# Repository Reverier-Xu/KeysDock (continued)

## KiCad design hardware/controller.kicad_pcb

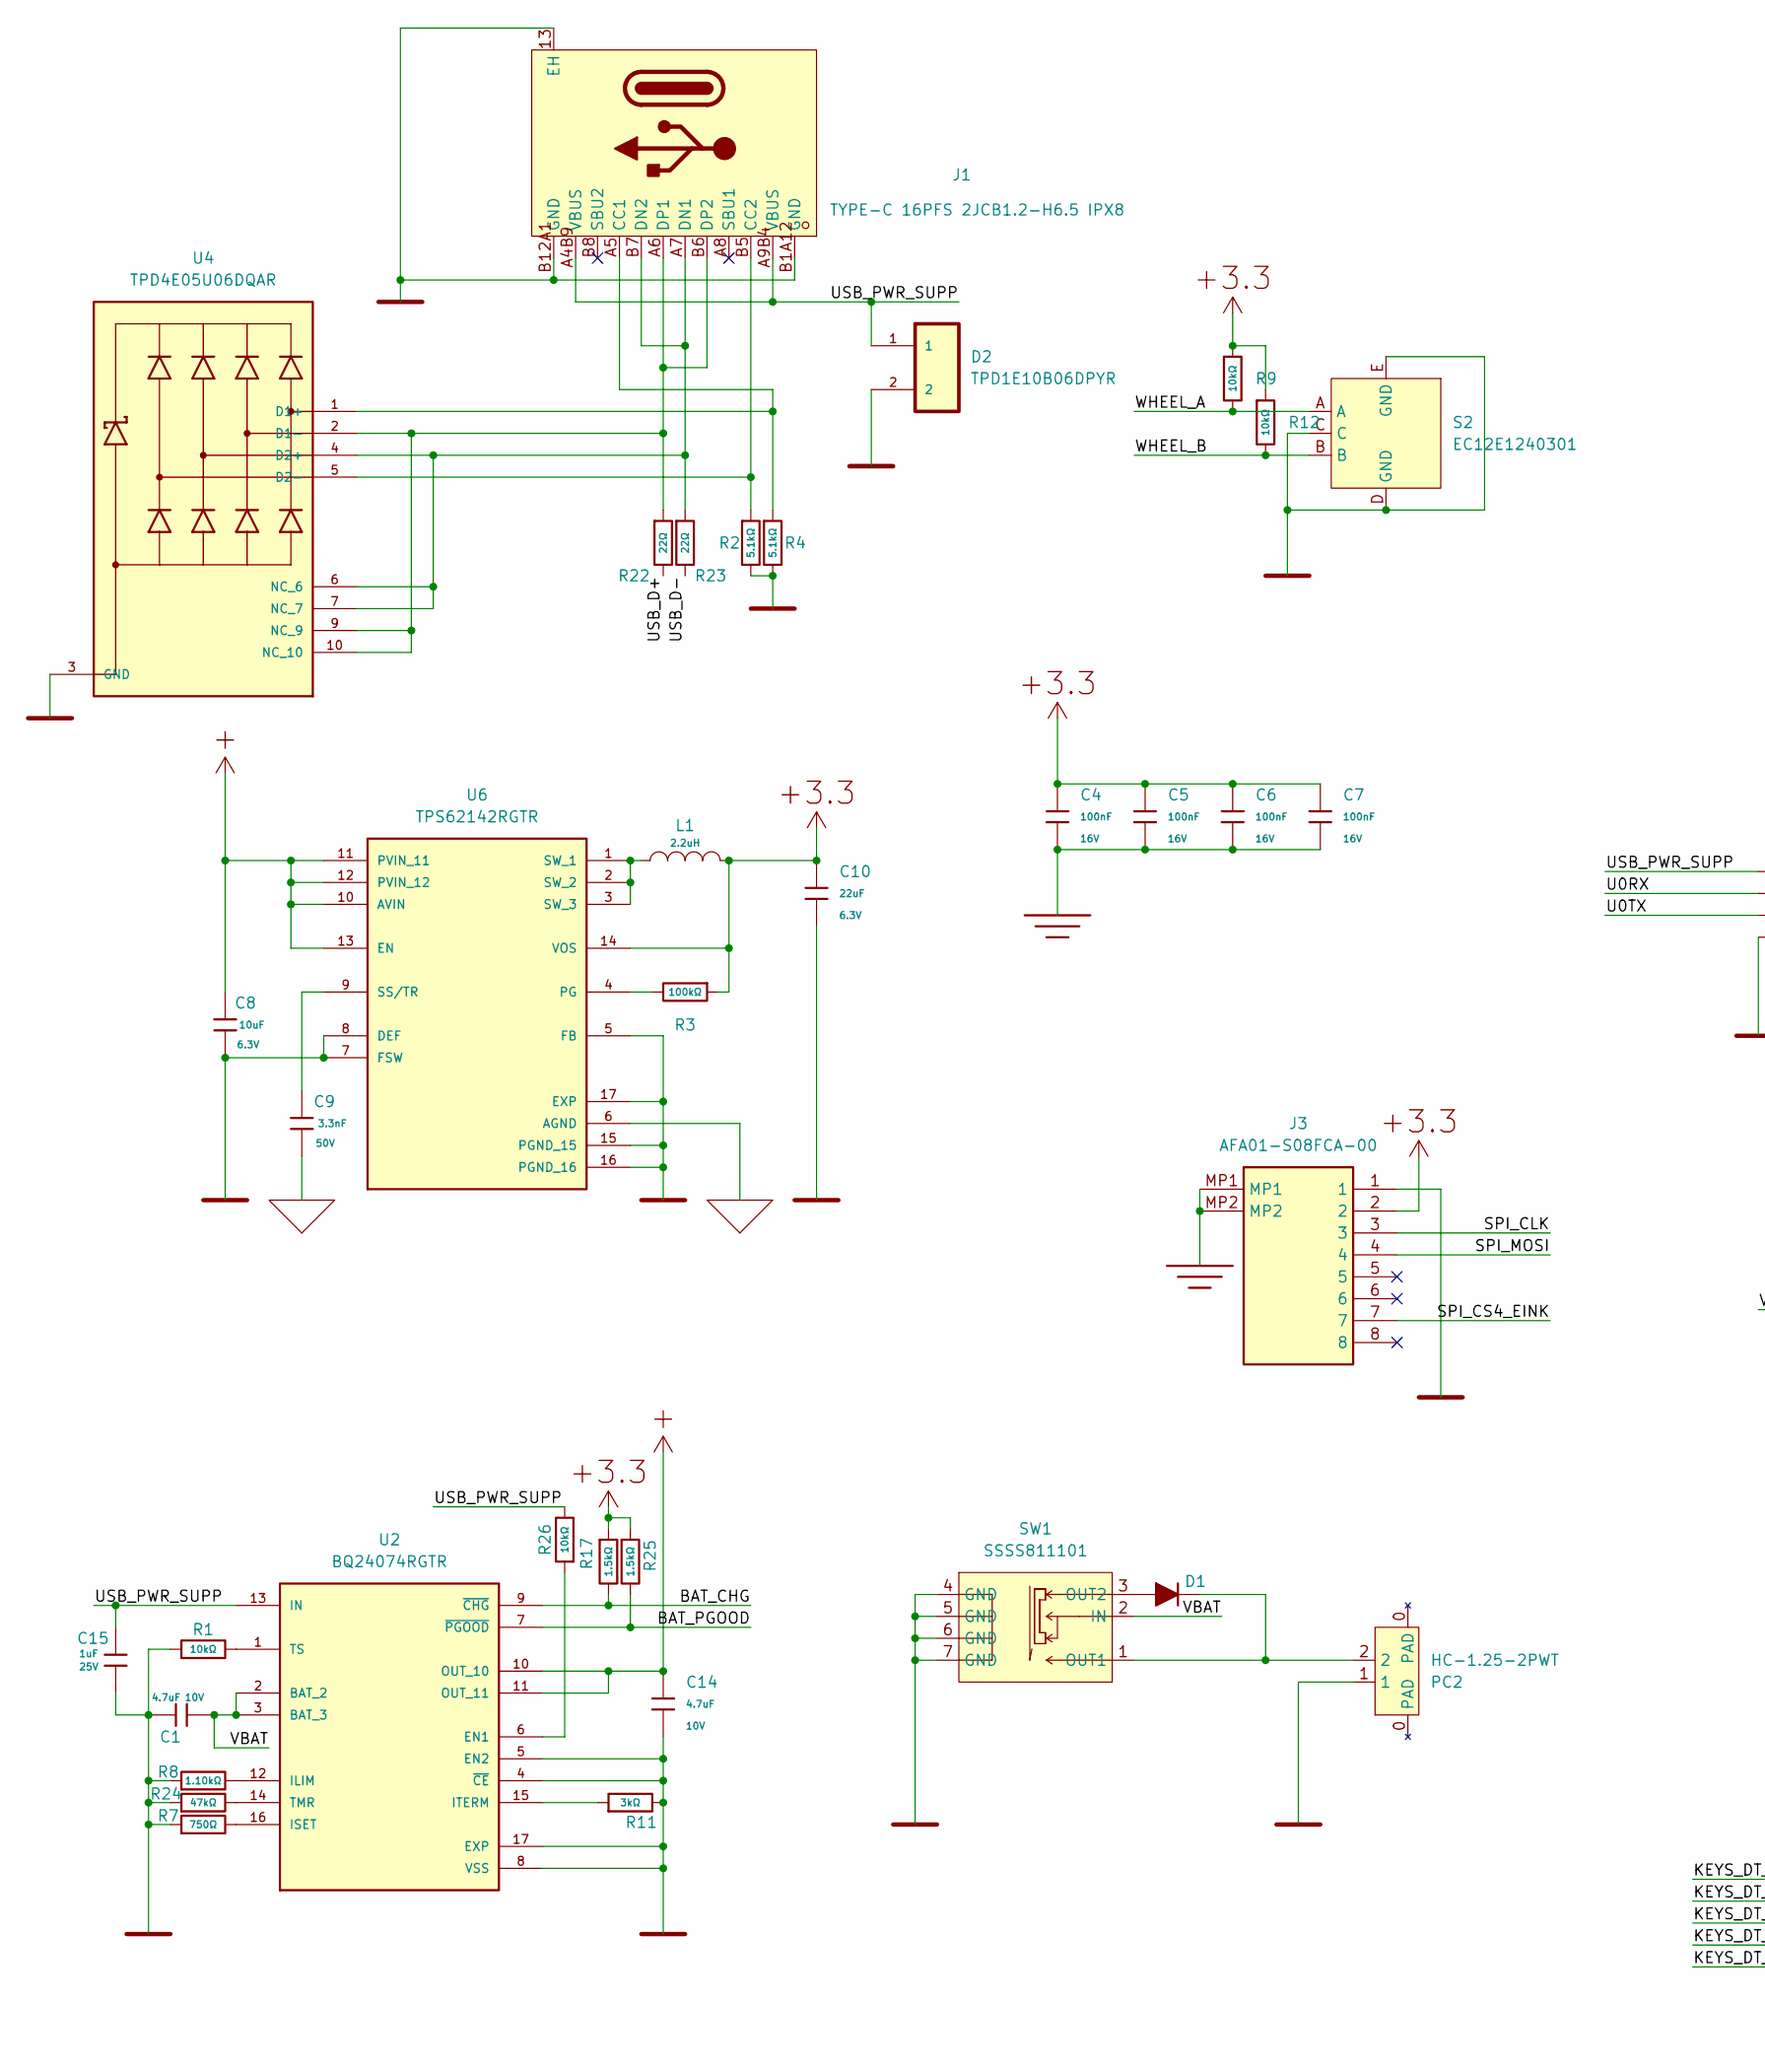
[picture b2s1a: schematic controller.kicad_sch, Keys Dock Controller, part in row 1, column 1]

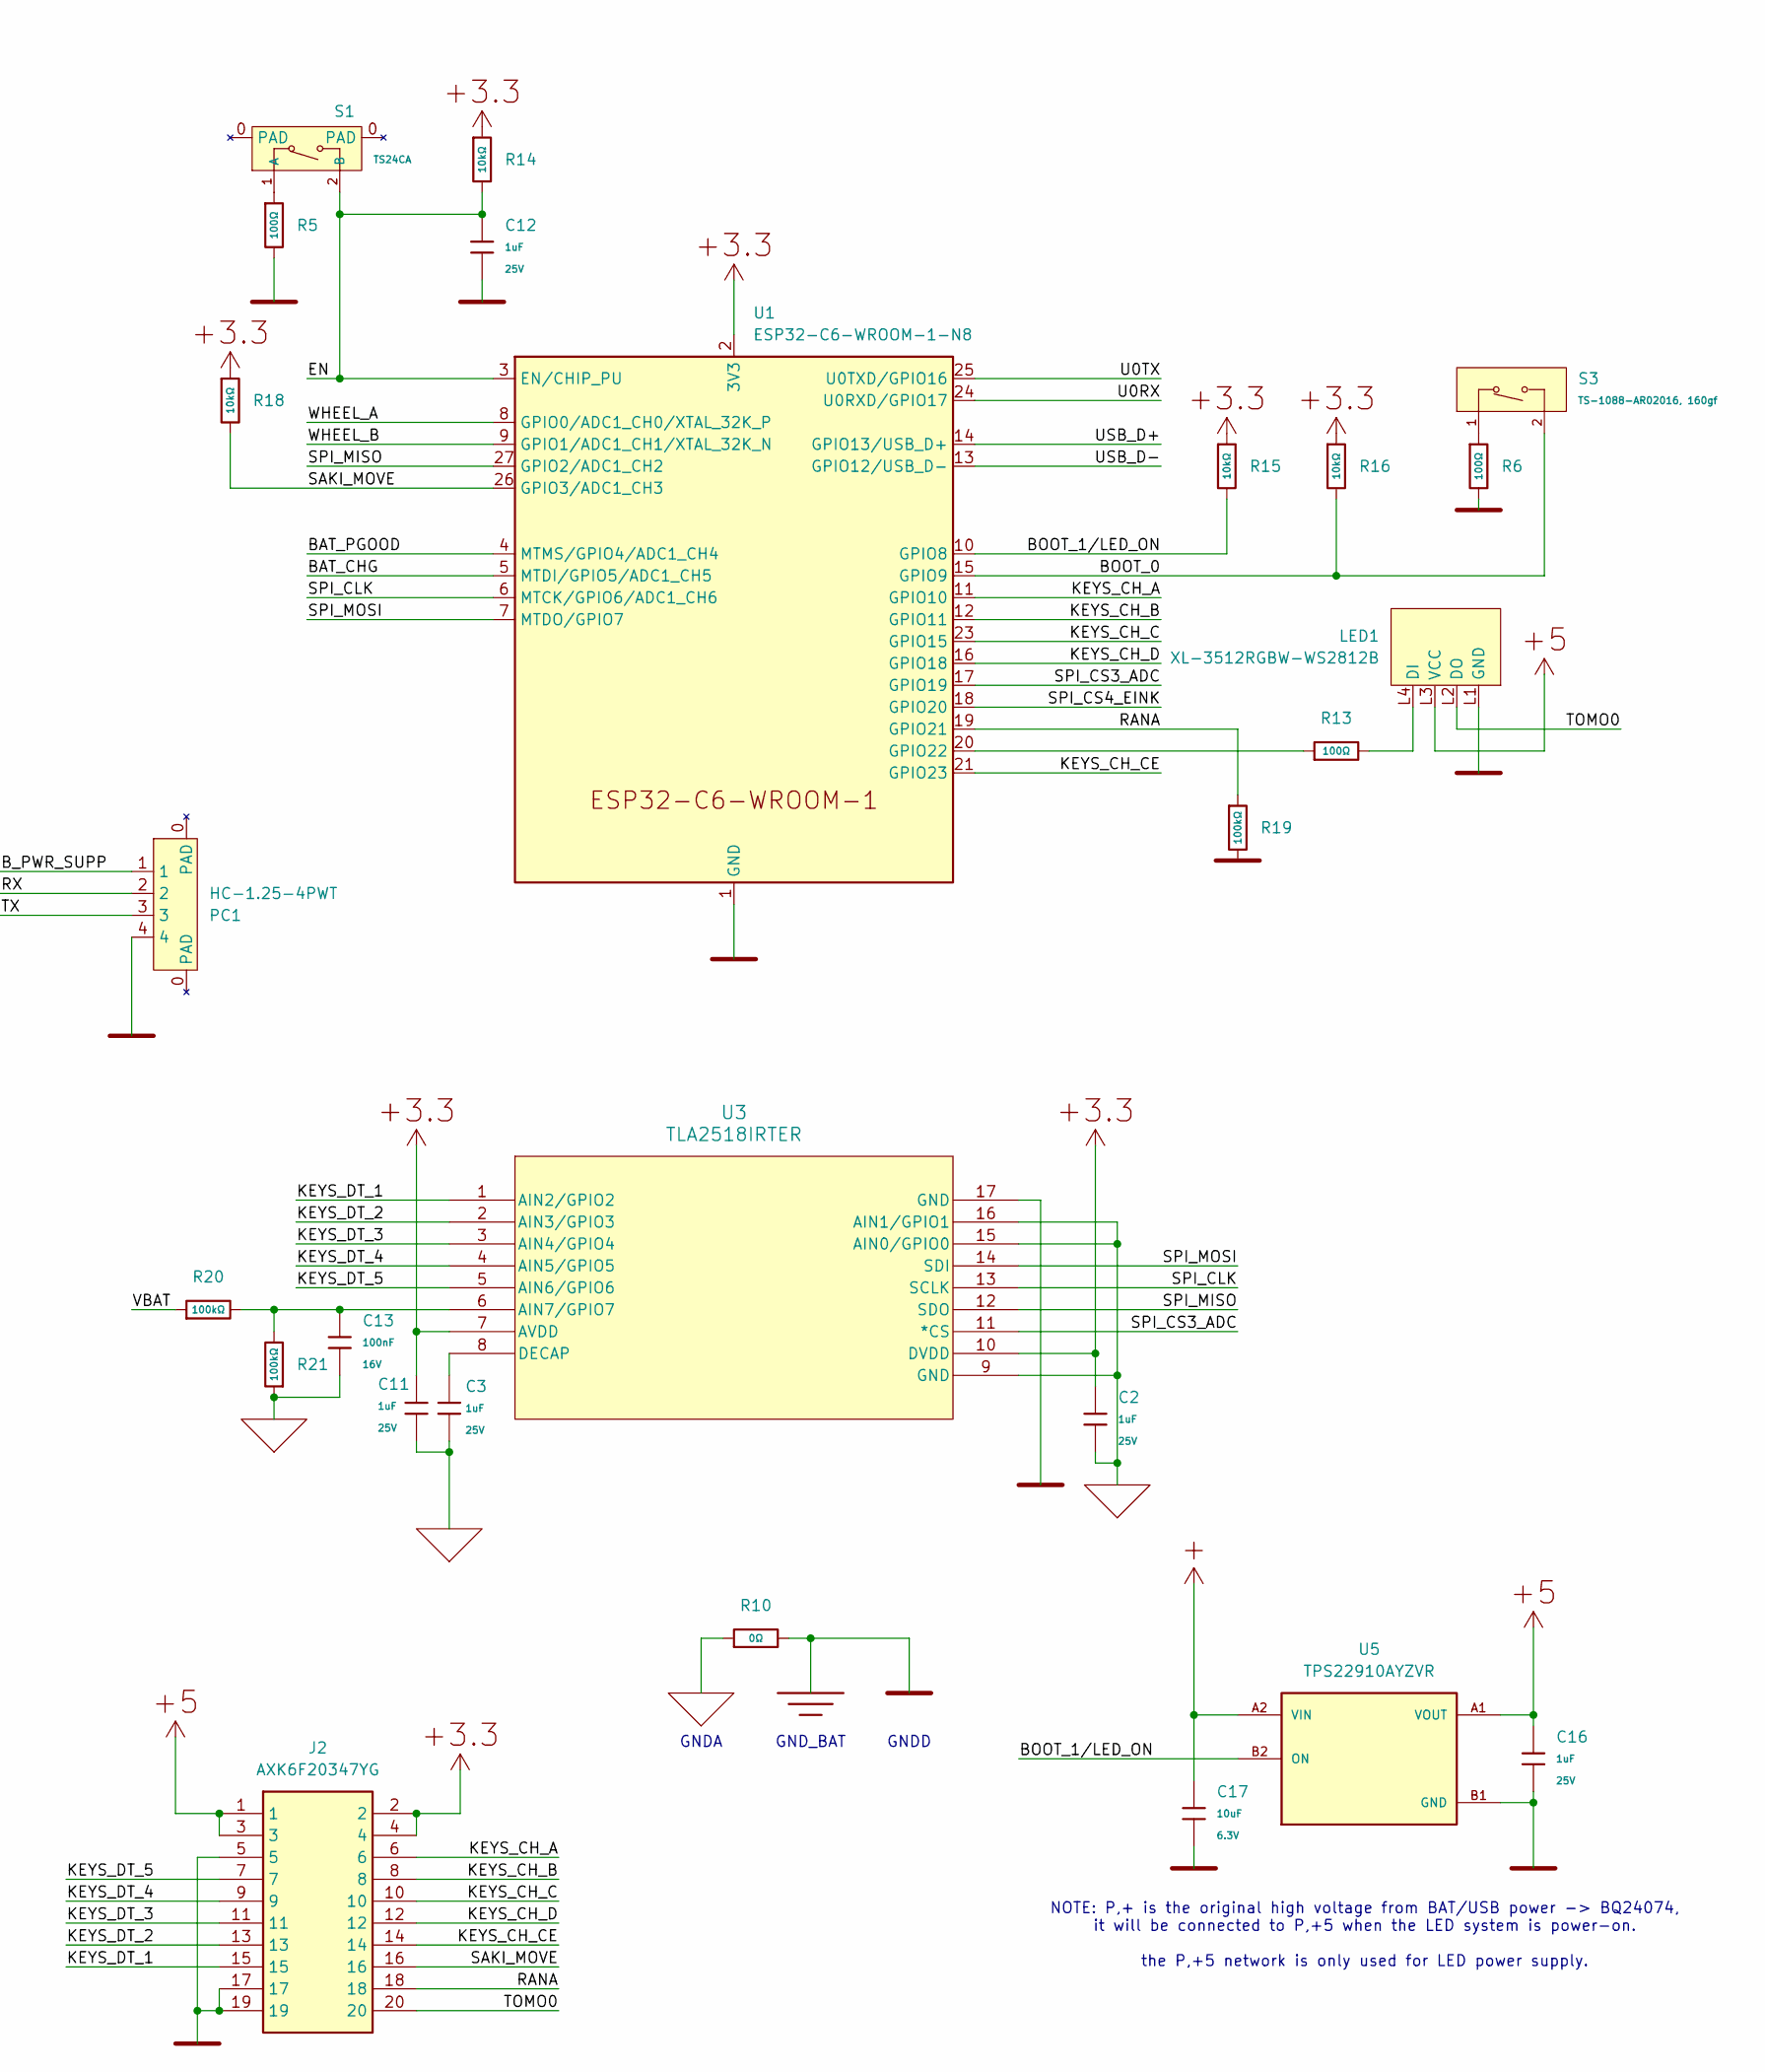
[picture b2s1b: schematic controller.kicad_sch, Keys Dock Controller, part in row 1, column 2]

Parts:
C1, C14: 4.7uF; C_0402; Voltage Rated 10V; Tolerance ±20%; Part CL05A475MP5NRNC; LCSC C23733
C2, C3, C11, C12, C15, C16: 1uF; C_0402; Voltage Rated 25V; Tolerance ±10%; Part CL05A105KA5NQNC; LCSC C52923
C4, C5, C6, C7, C13: 100nF; C_0402; Voltage Rated 16V; Tolerance ±10%; Part CL05B104KO5NNNC; LCSC C1525
C8, C17: 10uF; C_0402; Voltage Rated 6.3V; Tolerance ±20%; Part CL05A106MQ5NUNC; LCSC C15525
C9: 3.3nF; C_0402; Voltage Rated 50V; Tolerance ±10%; Part CL05B332KB5NNNC; LCSC C26404
C10: 22uF; C_0402; Voltage Rated 6.3V; Tolerance ±20%; Part CL05A226MQ5QUNC; LCSC C105226
D1: SM4007PL; D_SOD-123FL; LCSC C78741
D2: TPD1E10B06DPYR; DIO_TPD1E05U06DPYR; LCSC C48260
J1: TYPE-C 16PFS 2JCB1.2-H6.5 IPX8; USB-C-SMD_SHOUHAN_TYPE-C-16PFS-2JCB1.2-H6.5; Current Rating - Power 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 3A; LCSC C3020046
J2: AXK6F20347YG; Manufacturer_Part_Number AXK6F20347YG; Mouser Part Number 769-AXK6F20347YG
J3: AFA01-S08FCA-00; Manufacturer_Part_Number AFA01-S08FCA-00; LCSC C262755
L1: 2.2uH; IND-SMD_L2.5-W2.0_MHCHL2520; Tolerance ±20%; Part FTC252012S2R2MBCA; LCSC C5832372
LED1: XL-3512RGBW-WS2812B; LCSC C49237874
PC1: HC-1.25-4PWT; LCSC C2845381
PC2: HC-1.25-2PWT; LCSC C2845379
R1, R9, R12, R14, R15, R16, R18, R26: 10kΩ; R_0402; Overload Voltage (Max) 50V; Tolerance ±1%; Part 0402WGF1002TCE; LCSC C25744
R2, R4: 5.1kΩ; R_0402; Overload Voltage (Max) 50V; Tolerance ±1%; Part 0402WGJ0512TCE; LCSC C25941
R3, R19, R20, R21: 100kΩ; R_0402; Overload Voltage (Max) 50V; Tolerance ±1%; Part 0402WGF1003TCE; LCSC C25741
R5, R6, R13: 100Ω; R_0402; Overload Voltage (Max) 50V; Tolerance ±1%; Part 0402WGF1000TCE; LCSC C25076
R7: 750Ω; R_0402; Overload Voltage (Max) 50V; Tolerance ±1%; Part 0402WGF7500TCE; LCSC C25132
R8: 1.10kΩ; R_0402; Overload Voltage (Max) 50V; Tolerance ±1%; Part 0402WGF1101TCE; LCSC C25860
R10: 0Ω; R_0402; Overload Voltage (Max) 50V; Tolerance ±1%; Part 0402WGF0000TCE; LCSC C17168
R11: 3kΩ; R_0402; Overload Voltage (Max) 50V; Tolerance ±1%; Part 0402WGF3001TCE; LCSC C25784
R17, R25: 1.5kΩ; R_0402; Overload Voltage (Max) 50V; Tolerance ±1%; Part 0402WGF1501TCE; LCSC C25867
R22, R23: 22Ω; R_0402; Overload Voltage (Max) 50V; Tolerance ±1%; Part 0402WGF220JTCE; LCSC C25092
R24: 47kΩ; R_0402; Overload Voltage (Max) 50V; Tolerance ±1%; Part 0402WGF4702TCE; LCSC C25792
S1: TS24CA; Voltage Rating (Dc) 12V; Part TS-1088-AR02016; LCSC C393942
S2: EC12E1240301; LCSC C351235
S3: TS-1088-AR02016, 160gf; SW_TS-1088-AR02016; Voltage Rating (Dc) 12V; Part TS-1088-AR02016; LCSC C720477
SW1: SSSS811101; SW-SMD_SSSS811101; LCSC C109335
U1: ESP32-C6-WROOM-1-N8; ESP32-C6-WROOM-1
U2: BQ24074RGTR; QFN50P300X300X80-17N; PARTREV M; LCSC C54313
U3: TLA2518IRTER; QFN50P300X300X80-17N; LCSC C1855741
U4: TPD4E05U06DQAR; IC_TPD4E05U06DQAR; PARTREV N; LCSC C138714
U5: TPS22910AYZVR; BGA4N50P2X2_88X88X50N; PARTREV F; LCSC C205966
U6: TPS62142RGTR; QFN50P300X300X80-17N; PARTREV E; LCSC C129331

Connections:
/BAT_CHG: R17.2, U1.5 (MTDI/GPIO5/ADC1_CH5), U2.9 (~CHG)
/BAT_PGOOD: R25.2, U1.4 (MTMS/GPIO4/ADC1_CH4), U2.7 (~PGOOD)
/BOOT_0: R16.2, S3.2 (B), U1.15 (GPIO9)
/BOOT_1/LED_ON: R15.2, U1.10 (GPIO8), U5.B2 (ON)
/EN: C12.1, R14.2, S1.2 (B), U1.3 (EN/CHIP_PU)
/KEYS_CH_A: J2.6, U1.11 (GPIO10)
/KEYS_CH_B: J2.8, U1.12 (GPIO11)
/KEYS_CH_C: J2.10, U1.23 (GPIO15)
/KEYS_CH_CE: J2.14, U1.21 (GPIO23)
/KEYS_CH_D: J2.12, U1.16 (GPIO18)
/KEYS_DT_1: J2.15, U3.1 (AIN2/GPIO2)
/KEYS_DT_2: J2.13, U3.2 (AIN3/GPIO3)
/KEYS_DT_3: J2.11, U3.3 (AIN4/GPIO4)
/KEYS_DT_4: J2.9, U3.4 (AIN5/GPIO5)
/KEYS_DT_5: J2.7, U3.5 (AIN6/GPIO6)
/RANA: J2.18, R19.1, U1.19 (GPIO21)
/SAKI_MOVE: J2.16, R18.2, U1.26 (GPIO3/ADC1_CH3)
/SPI_CLK: J3.3, U1.6 (MTCK/GPIO6/ADC1_CH6), U3.13 (SCLK)
/SPI_CS3_ADC: U1.17 (GPIO19), U3.11 (*CS)
/SPI_CS4_EINK: J3.7, U1.18 (GPIO20)
/SPI_MISO: U1.27 (GPIO2/ADC1_CH2), U3.12 (SDO)
/SPI_MOSI: J3.4, U1.7 (MTDO/GPIO7), U3.14 (SDI)
/TOMO0: J2.20, LED1.L2 (DO)
/U0RX: PC1.2, U1.24 (U0RXD/GPIO17)
/U0TX: PC1.3, U1.25 (U0TXD/GPIO16)
/USB_D+: R22.2, U1.14 (GPIO13/USB_D+)
/USB_D-: R23.2, U1.13 (GPIO12/USB_D-)
/USB_PWR_SUPP: C15.1, D2.1, J1.A4B9 (VBUS), J1.A9B4 (VBUS), PC1.1, R26.2, U2.13 (IN)
/VBAT: C1.2, R20.1, SW1.2 (IN), U2.2 (BAT_2), U2.3 (BAT_3)
/WHEEL_A: R9.2, S2.A, U1.8 (GPIO0/ADC1_CH0/XTAL_32K_P)
/WHEEL_B: R12.2, S2.B, U1.9 (GPIO1/ADC1_CH1/XTAL_32K_N)
unnamed: D1.2 (A), SW1.3 (OUT2)
unnamed: D1.1 (K), PC2.2, SW1.1 (OUT1)
unnamed: J1.A5 (CC1), R4.1, U4.1 (D1+)
unnamed: J1.B5 (CC2), R2.1, U4.5 (D2-)
unnamed: J1.A7 (DN1), J1.B7 (DN2), R23.1, U4.4 (D2+), U4.6 (NC_6), U4.7 (NC_7)
unnamed: J1.A6 (DP1), J1.B6 (DP2), R22.1, U4.2 (D1-), U4.9 (NC_9), U4.10 (NC_10)
unnamed: LED1.L4 (DI), R13.2
unnamed: R5.1, S1.1 (A)
unnamed: R6.1, S3.1 (A)
unnamed: R13.1, U1.20 (GPIO22)
unnamed: R26.1, U2.6 (EN1)
unnamed: R8.2, U2.12 (ILIM)
unnamed: R7.2, U2.16 (ISET)
unnamed: R11.1, U2.15 (ITERM)
unnamed: R24.2, U2.14 (TMR)
unnamed: R1.2, U2.1 (TS)
unnamed: C13.1, R20.2, R21.2, U3.6 (AIN7/GPIO7)
unnamed: C3.1, U3.8 (DECAP)
unnamed: R3.2, U6.4 (PG)
unnamed: C9.1, U6.9 (SS/TR)
unnamed: L1.1, U6.1 (SW_1), U6.2 (SW_2), U6.3 (SW_3)
P,+: C8.1, C14.2, C17.2, U2.10 (OUT_10), U2.11 (OUT_11), U5.A2 (VIN), U6.10 (AVIN), U6.11 (PVIN_11), U6.12 (PVIN_12), U6.13 (EN)
P,+3.3: C2.1, C4.1, C5.1, C6.1, C7.1, C10.1, C11.2, J2.2, J2.4, J3.2, L1.2, R3.1, R9.1, R12.1, R14.1, R15.1, R16.1, R17.1, R18.1, R25.1, U1.2 (3V3), U3.7 (AVDD), U3.10 (DVDD), U6.14 (VOS)
P,+5: C16.2, J2.1, J2.3, LED1.L3 (VCC), U5.A1 (VOUT)
P,E: C1.1, C4.2, C5.2, C6.2, C7.2, C8.2, C10.2, C12.2, C14.1, C15.2, C16.1, C17.1, D2.2, J1.13 (EH), J1.B1A12 (GND), J1.B12A1 (GND), J2.5, J2.17, J2.19, J3.1, J3.MP1, J3.MP2, LED1.L1 (GND), PC1.4, PC2.1, R1.1, R2.2, R4.2, R5.2, R6.2, R7.1, R8.1, R10.2, R11.2, R19.2, R24.1, S2.C, S2.D (GND), S2.E (GND), SW1.4 (GND), SW1.5 (GND), SW1.6 (GND), SW1.7 (GND), U1.1 (GND), U1.28 (GND), U1.29 (GND), U2.4 (~CE), U2.5 (EN2), U2.8 (VSS), U2.17 (EXP), U3.17 (GND), U4.3 (GND), U4.8 (GND), U5.B1 (GND), U6.5 (FB), U6.7 (FSW), U6.8 (DEF), U6.15 (PGND_15), U6.16 (PGND_16), U6.17 (EXP)
P,GND: C2.2, C3.2, C9.2, C11.1, C13.2, R10.1, R21.1, U3.9 (GND), U3.15 (AIN0/GPIO0), U3.16 (AIN1/GPIO1), U6.6 (AGND)

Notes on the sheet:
GNDD
GNDA
GND_BAT
NOTE: P,+ is the original high voltage from BAT/USB power -> BQ24074, it will be connected to P,+5 when the LED system is power-on. the P,+5 network is only used for LED power supply.

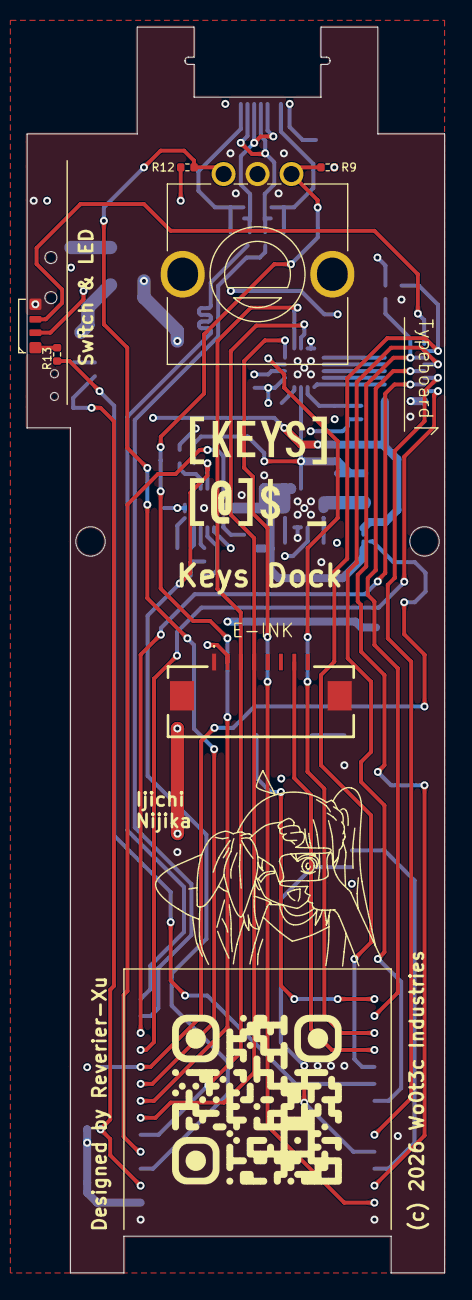
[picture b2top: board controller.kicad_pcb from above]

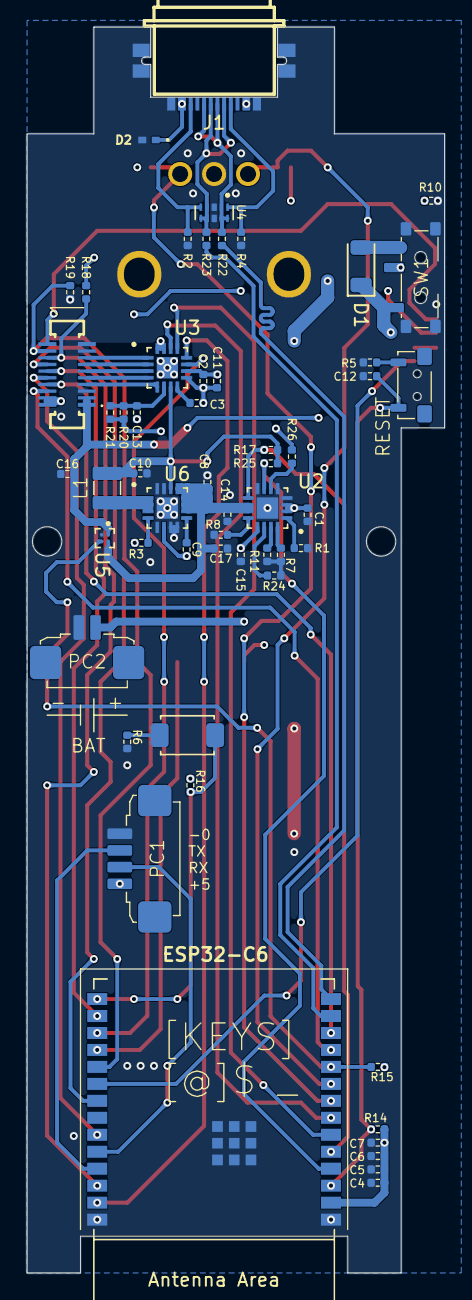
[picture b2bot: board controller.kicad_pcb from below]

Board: 4 copper layers, 31.2 x 93.2 mm, 62 parts (56 on the bottom side), 57 nets.

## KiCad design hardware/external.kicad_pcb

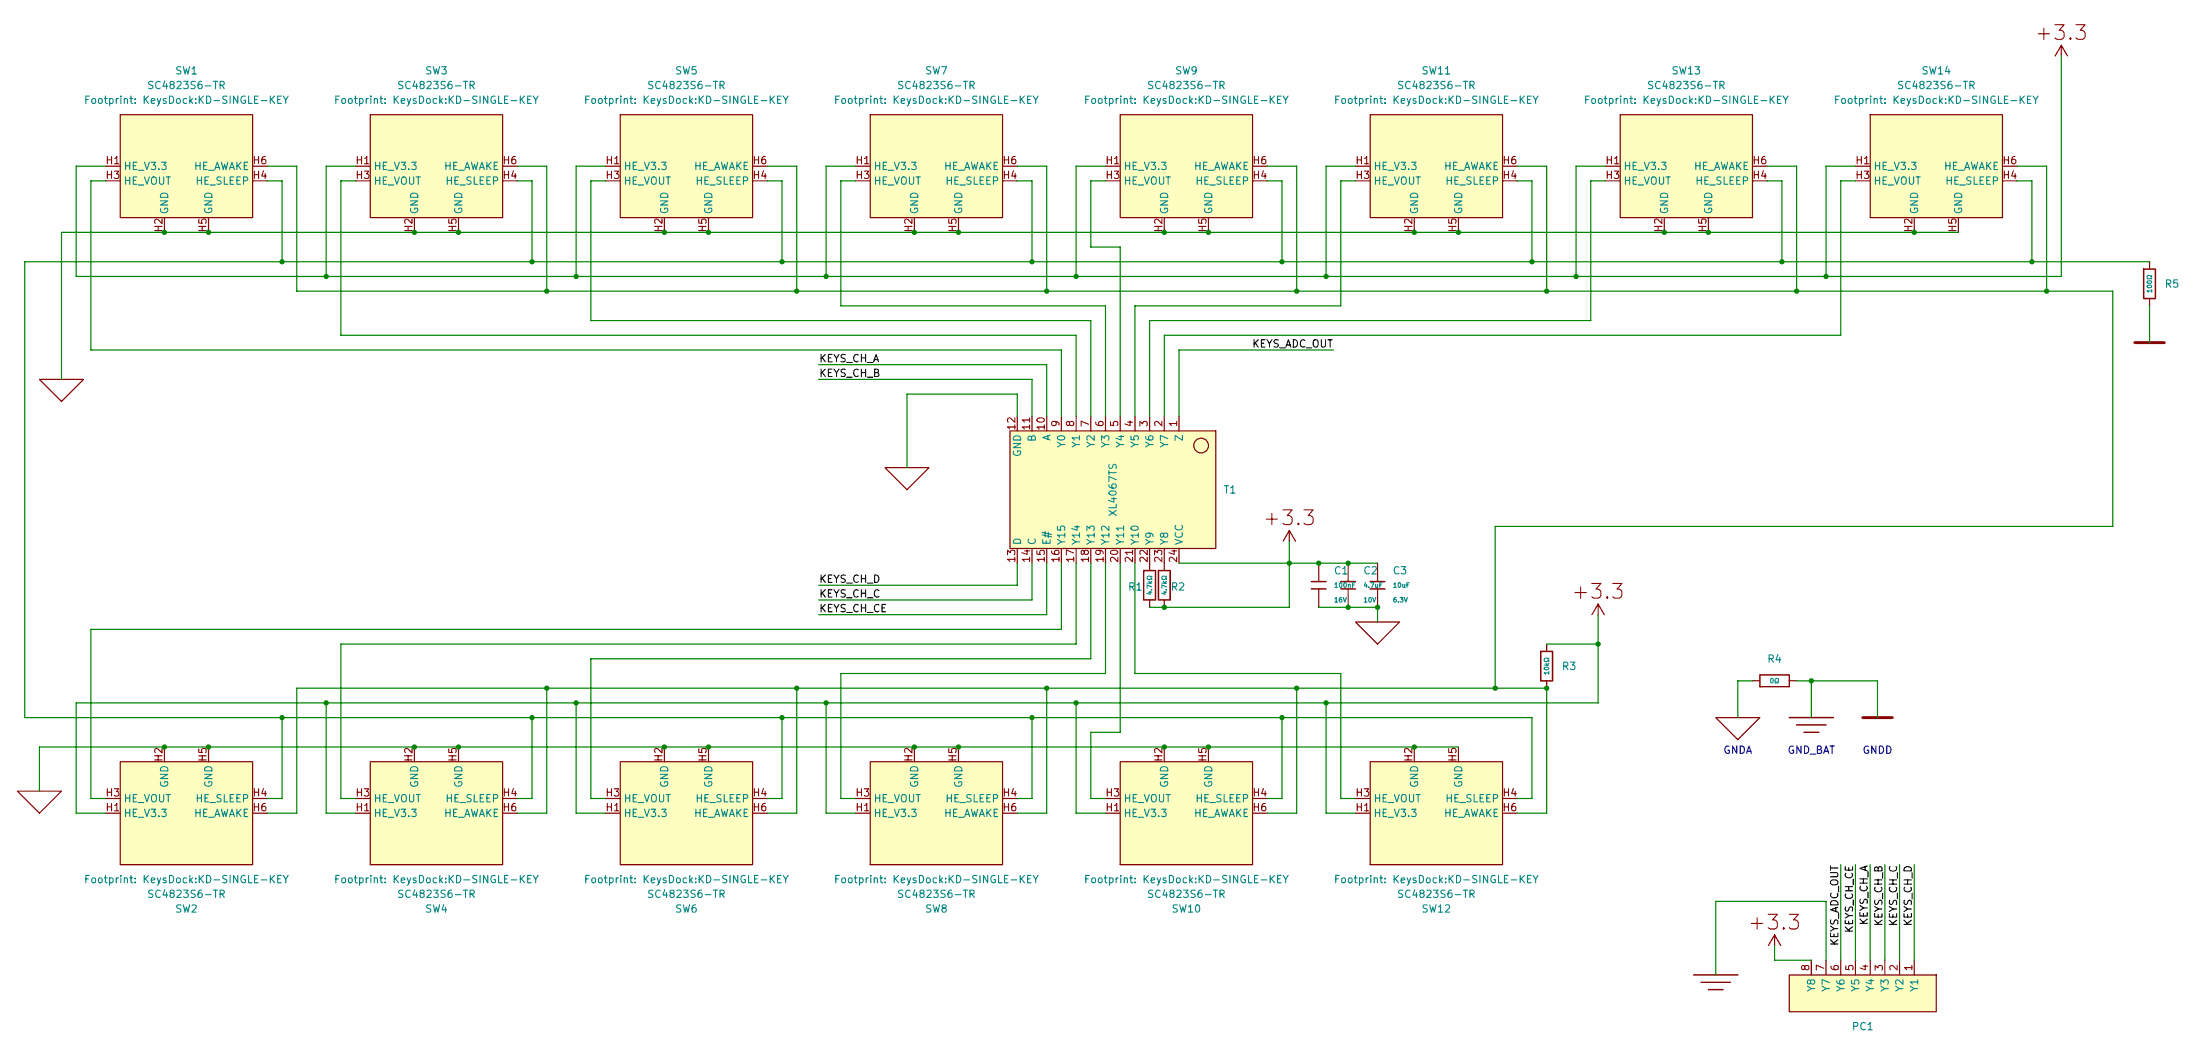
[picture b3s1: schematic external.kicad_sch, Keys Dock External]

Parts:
C1: 100nF; C_0402; Voltage Rated 16V; Tolerance ±10%; Part CL05B104KO5NNNC; LCSC C1525
C2: 4.7uF; C_0402; Voltage Rated 10V; Tolerance ±20%; Part CL05A475MP5NRNC; LCSC C23733
C3: 10uF; C_0402; Voltage Rated 6.3V; Tolerance ±20%; Part CL05A106MQ5NUNC; LCSC C15525
PC1: POGOPIN-8P-HS
R1, R2: 4.7kΩ; R_0402; Overload Voltage (Max) 50V; Tolerance ±1%; Part 0402WGF4701TCE; LCSC C25900
R3: 10kΩ; R_0402; Overload Voltage (Max) 50V; Tolerance ±1%; Part 0402WGF1002TCE; LCSC C25744
R4: 0Ω; R_0402; Overload Voltage (Max) 50V; Tolerance ±1%; Part 0402WGF0000TCE; LCSC C17168
R5: 100Ω; R_0402; Overload Voltage (Max) 50V; Tolerance ±1%; Part 0402WGF1000TCE; LCSC C25076
SW1, SW2, SW3, SW4, SW5, SW6, SW7, SW8, SW9, SW10, SW11, SW12, SW13, SW14: SC4823S6-TR; KD-SINGLE-KEY; LCSC C52021064
T1: XL4067TS; LCSC C41427445

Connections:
/KEYS_ADC_OUT: PC1.6 (Y6), T1.1 (Z)
/KEYS_CH_A: PC1.4 (Y4), T1.10 (A)
/KEYS_CH_B: PC1.3 (Y3), T1.11 (B)
/KEYS_CH_C: PC1.2 (Y2), T1.14 (C)
/KEYS_CH_CE: PC1.5 (Y5), T1.15 (E#)
/KEYS_CH_D: PC1.1 (Y1), T1.13 (D)
unnamed: R3.2, SW1.H6 (HE_AWAKE), SW2.H6 (HE_AWAKE), SW3.H6 (HE_AWAKE), SW4.H6 (HE_AWAKE), SW5.H6 (HE_AWAKE), SW6.H6 (HE_AWAKE), SW7.H6 (HE_AWAKE), SW8.H6 (HE_AWAKE), SW9.H6 (HE_AWAKE), SW10.H6 (HE_AWAKE), SW11.H6 (HE_AWAKE), SW12.H6 (HE_AWAKE), SW13.H6 (HE_AWAKE), SW14.H6 (HE_AWAKE)
unnamed: R5.1, SW1.H4 (HE_SLEEP), SW2.H4 (HE_SLEEP), SW3.H4 (HE_SLEEP), SW4.H4 (HE_SLEEP), SW5.H4 (HE_SLEEP), SW6.H4 (HE_SLEEP), SW7.H4 (HE_SLEEP), SW8.H4 (HE_SLEEP), SW9.H4 (HE_SLEEP), SW10.H4 (HE_SLEEP), SW11.H4 (HE_SLEEP), SW12.H4 (HE_SLEEP), SW13.H4 (HE_SLEEP), SW14.H4 (HE_SLEEP)
unnamed: SW1.H3 (HE_VOUT), T1.9 (Y0)
unnamed: SW2.H3 (HE_VOUT), T1.16 (Y15)
unnamed: SW3.H3 (HE_VOUT), T1.8 (Y1)
unnamed: SW4.H3 (HE_VOUT), T1.17 (Y14)
unnamed: SW5.H3 (HE_VOUT), T1.7 (Y2)
unnamed: SW6.H3 (HE_VOUT), T1.18 (Y13)
unnamed: SW7.H3 (HE_VOUT), T1.6 (Y3)
unnamed: SW8.H3 (HE_VOUT), T1.19 (Y12)
unnamed: SW9.H3 (HE_VOUT), T1.5 (Y4)
unnamed: SW10.H3 (HE_VOUT), T1.20 (Y11)
unnamed: SW11.H3 (HE_VOUT), T1.4 (Y5)
unnamed: SW12.H3 (HE_VOUT), T1.21 (Y10)
unnamed: SW13.H3 (HE_VOUT), T1.3 (Y6)
unnamed: SW14.H3 (HE_VOUT), T1.2 (Y7)
unnamed: R2.1, T1.23 (Y8)
unnamed: R1.1, T1.22 (Y9)
P,+3.3: C1.1, C2.1, C3.1, PC1.8 (Y8), R1.2, R2.2, R3.1, SW1.H1 (HE_V3.3), SW2.H1 (HE_V3.3), SW3.H1 (HE_V3.3), SW4.H1 (HE_V3.3), SW5.H1 (HE_V3.3), SW6.H1 (HE_V3.3), SW7.H1 (HE_V3.3), SW8.H1 (HE_V3.3), SW9.H1 (HE_V3.3), SW10.H1 (HE_V3.3), SW11.H1 (HE_V3.3), SW12.H1 (HE_V3.3), SW13.H1 (HE_V3.3), SW14.H1 (HE_V3.3), T1.24 (VCC)
P,E: PC1.7 (Y7), R4.2, R5.2
P,GND: C1.2, C2.2, C3.2, R4.1, SW1.H2 (GND), SW1.H5 (GND), SW2.H2 (GND), SW2.H5 (GND), SW3.H2 (GND), SW3.H5 (GND), SW4.H2 (GND), SW4.H5 (GND), SW5.H2 (GND), SW5.H5 (GND), SW6.H2 (GND), SW6.H5 (GND), SW7.H2 (GND), SW7.H5 (GND), SW8.H2 (GND), SW8.H5 (GND), SW9.H2 (GND), SW9.H5 (GND), SW10.H2 (GND), SW10.H5 (GND), SW11.H2 (GND), SW11.H5 (GND), SW12.H2 (GND), SW12.H5 (GND), SW13.H2 (GND), SW13.H5 (GND), SW14.H2 (GND), SW14.H5 (GND), T1.12 (GND)

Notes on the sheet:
GNDA
GND_BAT
GNDD

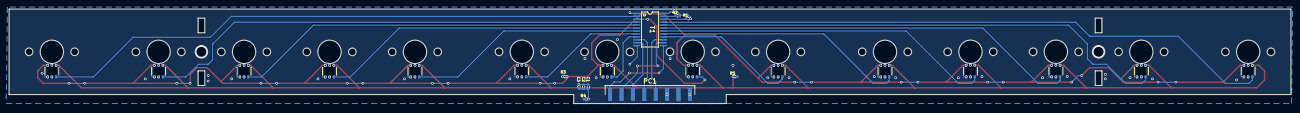
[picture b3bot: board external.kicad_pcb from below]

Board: 4 copper layers, 285.8 x 21.0 mm, 24 parts (10 on the bottom side), 27 nets.

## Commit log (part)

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2025-10-08 :tada: project started
2025-10-08 :sparkles: try background suit
2025-10-09 :construction: add keyboard layout
2025-10-10 :sparkles: update plate and backsuit
2025-10-10 :sparkles: finished plate
2025-10-11 :construction: may finish main design
2025-10-12 :sparkles: add side cover
2025-10-12 :sparkles: add step files
2025-10-12 :construction: add sidecover
2025-10-15 :sparkles: main board finished
2025-10-15 :memo: add readme.md
2025-10-15 :truck: move directory archs
2025-10-15 :sparkles: add logo
2025-10-15 :sparkles: add fonts
2025-10-15 :sparkles: add software links
2025-10-15 :truck: change LED maufactor
2025-10-15 :art: add logo to sidecover
2025-10-16 :sparkles: rename hardware design
2025-10-24 :construction: move to hall effect keyboard
2025-10-25 :sparkles: add keys website archs
2025-10-25 :construction: finish LED
2025-10-25 :sparkles: splash screen
2025-10-26 :truck: move to plug-able layout
2025-10-26 :sparkles: setup ide for software dev
2025-10-26 :tada: gugugaga, gugugaga, gugu! gaga!
2025-10-26 :construction: new suite kits design
2025-10-26 :construction: web hid driver dev
2025-10-27 :construction: web hid driver
2025-10-28 :truck: change to kicad
2025-10-28 :construction: change suitekits
2025-10-28 :memo: Add GNU GPL v3 license
    Added the GNU General Public License version 3 to the project.
2025-10-29 :memo: add doc and datasheets
2025-10-29 :construction: draw some components
2025-10-30 :construction: explode saki
2025-10-31 :fire: remove external adc, use internal adc io pins
2025-11-01 :construction: daily update
2025-11-03 :construction: controller pcb shape
2025-11-03 :construction: controller position
2025-11-04 :construction: some connectors
2025-11-04 :sparkles: add some components
2025-11-05 ADD TESTPAD
    ADD TESTPAD
2025-11-08 :recycle: refactor symbol lib
2025-11-08 :construction: sync components
2025-11-08 :construction: key position
2025-11-08 :construction: show all the 3d models
2025-11-09 :construction: typeboard routing
2025-11-14 :sparkles: finish 2-piece pcb design
2025-11-14 :fire: rework
2025-11-15 :sparkles: finish v6 typeboard design
2025-11-16 :construction: try controller
2025-11-16 :construction: add 4 layer
2025-11-16 :sparkles: rounded 3v3 route corner
2025-11-16 :arrow_up: update dependencies
2025-11-17 :construction: add backcover
2025-11-17 👆UPDATE SOME CONTROLLER LINE
2025-11-18 :construction: start firmware
2025-11-23 :construction: controller board
2025-11-25 :sparkles: add ijichi nijika drawings
2025-11-28 :construction: add controller switchs
2025-11-30 :construction: run DRC on controller board
2025-11-30 :construction: lock state in frontend
2025-11-30 :construction: i18n updates
2025-12-02 :arrow: chamfer suitkits
2025-12-03 :recycle: refine layers
2025-12-06 :memo: reviewed by hankz
2025-12-09 :construction: add capacitors to ADC pin
2025-12-13 :construction: add external board init
2025-12-13 :sparkles: init keysdock firmware
2025-12-14 :sparkles: external board design
2025-12-19 :sparkles: add CH334P & CH343P to components library
2025-12-27 :sparkles: add battery management
2025-12-27 :sparkles: USB hub & USB2UART
2025-12-27 :construction: change power ic & switch
2025-12-27 :fire: use symlinks for doc
2025-12-28 :construction: try construct power supply & charging
2025-12-29 :sparkles: add battery management (#1)
2025-12-29 :sparkles: refine capacitors and crystals, finish charge chip
2025-12-29 :fire: reduce battery size
2025-12-31 :sparkles: finish pcb layout of controller
2026-01-01 :fire: remove CH-series chips and use legacy UART
2026-01-02 :sparkles: use side reset button
2026-01-02 :sparkles: finish all hardware designs except external
2026-01-02 :sparkles: finish all hardware designs
2026-01-02 :sparkles: add step file for pcb
2026-01-02 :sparkles: add silk tips for external board
2026-01-03 :sparkles: add sheet template
2026-01-03 :sparkles: assembly all the part!
2026-01-03 :sparkles: update sidecover
2026-01-03 :memo: update readme.md
2026-01-06 :art: improve LED positions
2026-01-06 :see_no_evil: ignore object format files
2026-01-06 :tada: in-dev 0.2.7
2026-01-06 :sparkles: add package design
2026-01-07 :sparkles: add testboard
2026-01-08 :sparkles: add bom table
2026-01-09 :construction: blender modeling
2026-01-22 :bug: fix switch hole
2026-02-12 :construction: panelize all boards
2026-02-13 :construction_worker: use fat LTO to produce smaller firmware
2026-03-22 :fire: remove panelized one
2026-03-22 :art: let AGENT to review hardware designs
2026-03-22 :arrow_up: update to KiCAD 10.0
2026-03-23 :bug: improve hardware design
2026-03-23 :sparkles: esd protection for type-c
2026-03-24 :fire: remove old optimize plan
2026-03-24 :sparkles: sync testpad
2026-03-24 :zap: improve led power supply
2026-03-25 :bug: fix L1
2026-03-27 :bug: fix BQ24074 usage in plan
2026-04-02 :fire: rollback to USB500
2026-04-02 :sparkles: change to TYPE-C 16P CB1.2
2026-04-03 :fire: remove backcover
2026-04-05 :fire: re-think 3d modeling
2026-04-07 :sparkles: rethink suitekits
2026-04-23 :fire: remove old files
2026-04-29 :construction: new board
2026-05-02 :construction: some chip layout
2026-05-05 :construction: awake and sleep lines
2026-05-07 :sparkles: finish keyboard
2026-05-09 :construction: lines for controller
2026-05-09 :sparkles: finish v4
2026-05-17 :sparkles: use net tie to construct GNDs
2026-06-06 :bug: connect plane gaps for USB_D+/-
2026-06-06 :art: add plate support for leds
2026-06-08 :memo: add contributors
2026-06-13 :sparkles: add capacitor for LEDs
2026-06-14 :construction: adjust led holes
2026-06-14 :construction: init spice tests
2026-06-18 :sparkles: finish pcb design
2026-06-20 :construction: use new plate stabilizer
2026-06-21 :construction: add spice tests
2026-06-21 :construction: sync new plate design
